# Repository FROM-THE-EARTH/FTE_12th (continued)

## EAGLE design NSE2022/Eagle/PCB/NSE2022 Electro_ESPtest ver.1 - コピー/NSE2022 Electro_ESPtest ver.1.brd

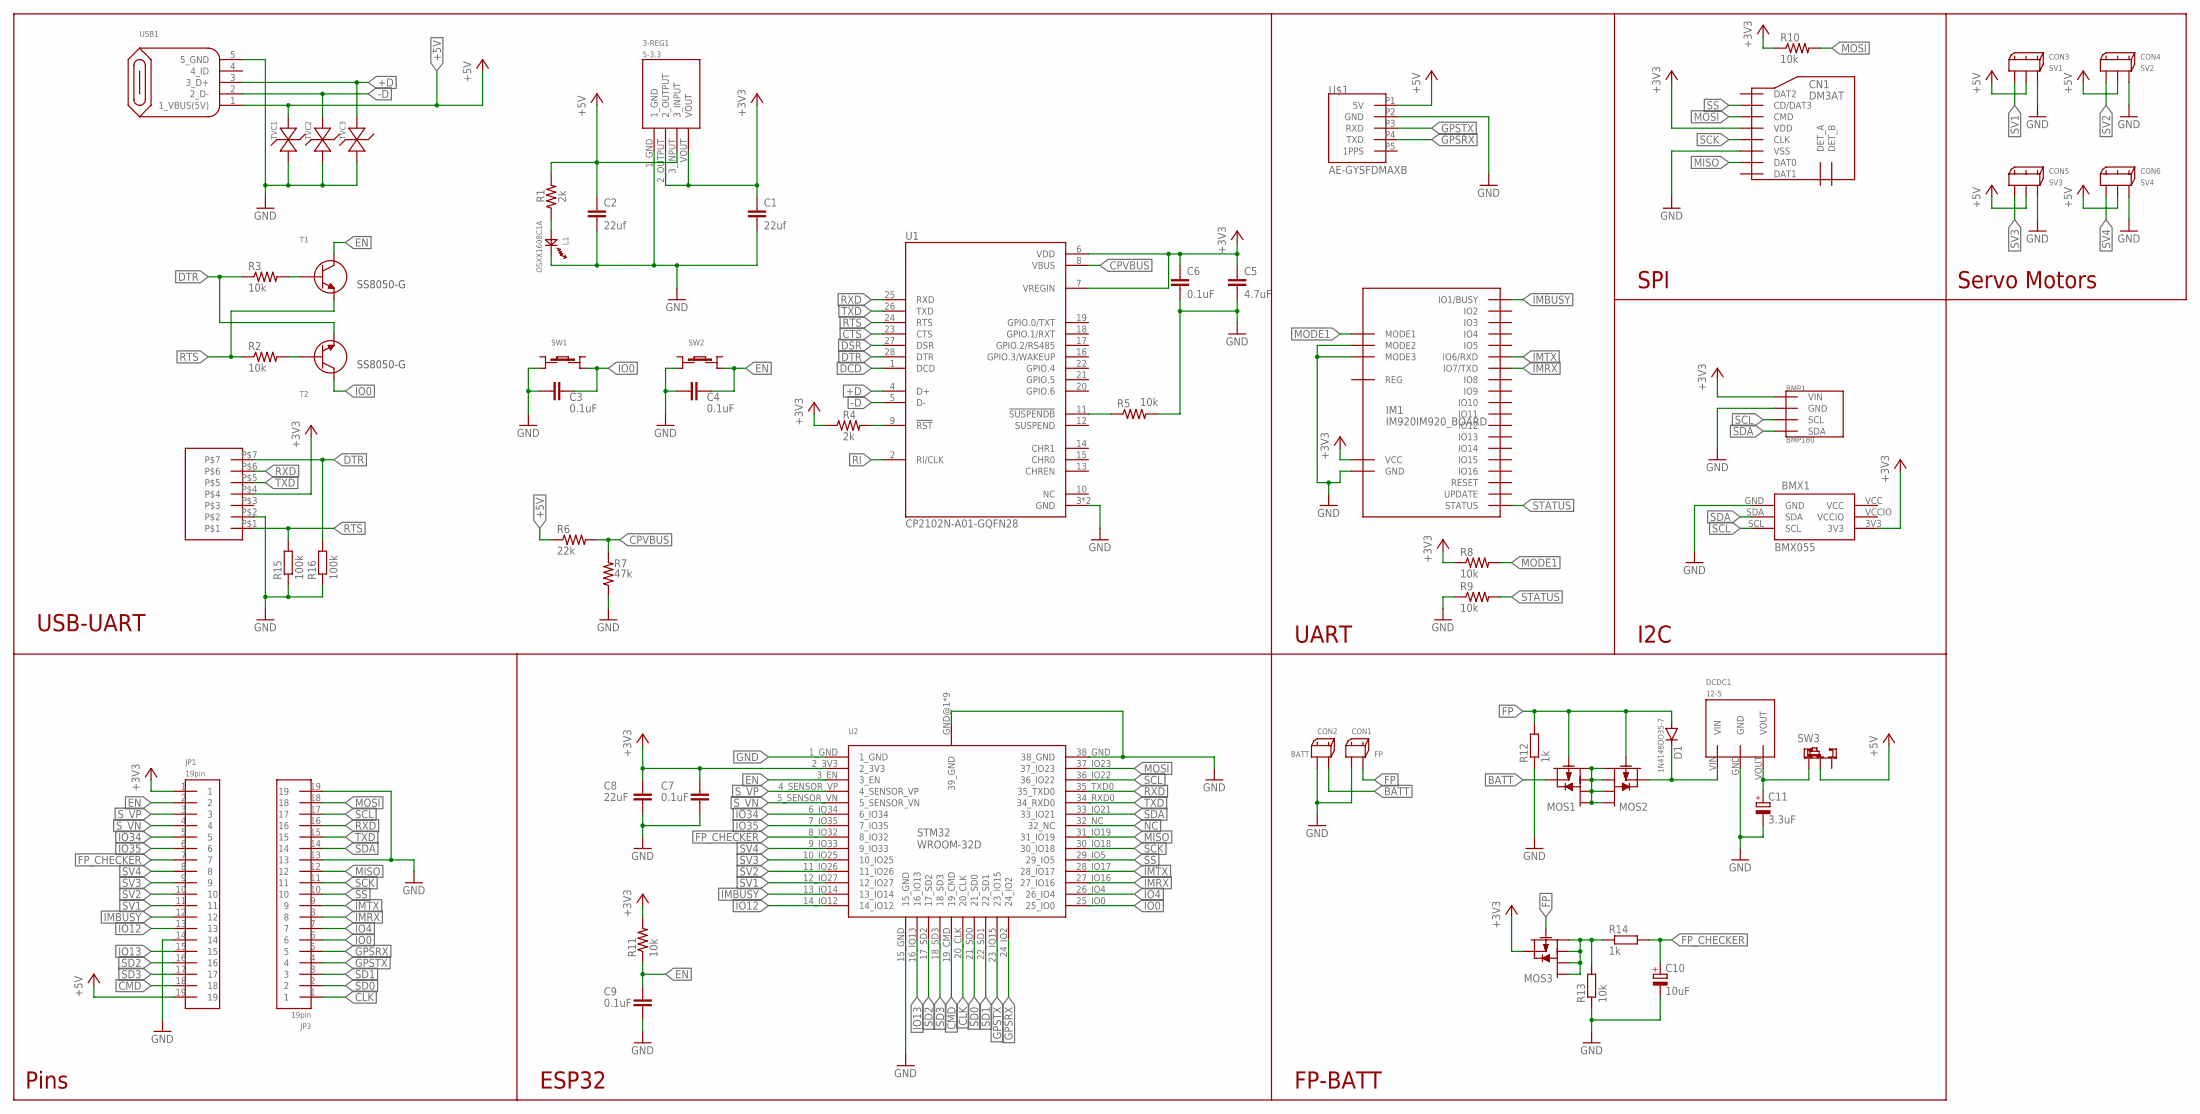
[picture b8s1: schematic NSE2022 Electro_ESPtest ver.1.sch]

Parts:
3-REG1: 5-3.3; AZ1117CH-3.3TRG1
BMP1: BMP180; GY-68
BMX1: BMX055
C1, C2: 22uf; C0603
C3, C4, C6, C7, C9: 0.1uF; C0603
C5: 4.7uF; C0402
C8: 22uF; C0603
C10: 10uF; E2,5-5
C11: 3.3uF; E2,5-5
CN1: DM3AT
CON1: FP; 2.5_MINI-SPOX_2PIN
CON2: BATT; 2.5_MINI-SPOX_2PIN
CON3: SV1; 2.5_MINI-SPOX_3PIN
CON4: SV2; 2.5_MINI-SPOX_3PIN
CON5: SV3; 2.5_MINI-SPOX_3PIN
CON6: SV4; 2.5_MINI-SPOX_3PIN
D1: 1N4148DO35-7; DO35-7
DCDC1: 12-5; 5V1A_M78AR05-1
IM1: IM920IM920_BOARD; IM920_BOARD
JP1, JP3: 19pin; 19_2.54
JP2: 7pin; 7_2.54
L1: OSXX1608C1A
MOS1, MOS2, MOS3: PCH_SSM6J808R; SSM6J808R
R1, R4: 2k; R0201
R2, R3, R5, R8, R9, R10, R11: 10k; R0201
R6: 22k; R0201
R7: 47k; R0201
R12, R14: 1k; 0207/10
R13: 10k; 0207/10
R15, R16: 100k; 0207/10
SW1, SW2: TS-06104
SW3: SRIDE_SWITCH
T1, T2: NPN_SS8050-G
TVC1, TVC2, TVC3: ESD5484FCT5G
U1: CP2102N-A01-GQFN28; QFN50P500X500X80-29N
U2: ESP32-WROOM-32D
U$1: AE-GYSFDMAXB
USB1: MICRO-B_ZX62R-B-5P

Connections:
+3V3: 3-REG1.2_OUTPUT, 3-REG1.VOUT, BMP1.P1 (VIN), BMX1.3V3, C1.1, C5.1, C6.1, C7.1, C8.1, CN1.VDD, IM1.IO23 (VCC), JP1.1, JP2.P$4, MOS3.S, R4.1, R8.1, R10.1, R11.2, U1.6 (VDD), U1.7 (VREGIN), U2.2_3V3
+5V: 3-REG1.3_INPUT, C2.1, CON3.2, CON4.2, CON5.2, CON6.2, JP1.19, R1.2, R6.1, SW3.LR, TVC1.2_AN, U$1.P1 (5V), USB1.1 (1_VBUS(5V))
+D: TVC3.2_AN, U1.4 (D+), USB1.3 (3_D+)
-D: TVC2.2_AN, U1.5 (D-), USB1.2 (2_D-)
BATT: CON2.2, MOS1.S
CLK: JP3.1, U2.20_CLK
CMD: JP1.18, U2.19_CMD
CPVBUS: R6.2, R7.2, U1.8 (VBUS)
CTS: U1.23 (CTS)
DCD: U1.1 (DCD)
DSR: U1.27 (DSR)
DTR: JP2.P$7, R3.1, R16.2, T2.2, U1.28 (DTR)
EN: C4.1, C9.1, JP1.2, R11.1, SW2.D, T1.3, U2.3_EN
FP: CON1.2, D1.A, MOS1.G, MOS2.G, MOS3.G, R12.2
FP_CHECKER: C10.+, JP1.7, R14.2, U2.8_IO32
GND: 3-REG1.1_GND, BMP1.P2 (GND), BMX1.GND, C1.2, C2.2, C3.2, C4.2, C5.2, C6.2, C7.2, C8.2, C9.2, C10.-, C11.-, CN1.VSS, CON1.1, CON2.1, CON3.3, CON4.3, CON5.3, CON6.3, DCDC1.GND, IM1.IO18 (MODE2), IM1.IO19 (MODE3), IM1.IO24 (GND), JP1.14, JP2.P$2, JP3.13, JP3.19, L1.CT, R5.2, R7.1, R9.1, R12.1, R13.1, R15.1, R16.1, SW1.B, SW2.B, TVC1.1_CT, TVC2.1_CT, TVC3.1_CT, U1.3 (GND), U1.29 (GND), U2.1_GND, U2.15_GND, U2.38_GND, U2.GND@1 (39_GND), U2.GND@2 (39_GND), U2.GND@3 (39_GND), U2.GND@4 (39_GND), U2.GND@5 (39_GND), U2.GND@6 (39_GND), U2.GND@7 (39_GND), U2.GND@8 (39_GND), U2.GND@9 (39_GND), U$1.P2 (GND), USB1.5 (5_GND)
GPSRX: JP3.5, U2.24_IO2, U$1.P4 (TXD)
GPSTX: JP3.4, U2.23_IO15, U$1.P3 (RXD)
IMBUSY: IM1.IO1 (IO1/BUSY), JP1.12, U2.13_IO14
IMRX: IM1.IO7 (IO7/TXD), JP3.8, U2.27_IO16
IMTX: IM1.IO6 (IO6/RXD), JP3.9, U2.28_IO17
IO0: C3.1, JP3.6, SW1.D, T2.3, U2.25_IO0
IO4: JP3.7, U2.26_IO4
IO12: JP1.13, U2.14_IO12
IO13: JP1.15, U2.16_IO13
IO34: JP1.5, U2.6_IO34
IO35: JP1.6, U2.7_IO35
MISO: CN1.DAT0, JP3.12, U2.31_IO19
MODE1: IM1.IO17 (MODE1), R8.2
MOSI: CN1.CMD, JP3.18, R10.2, U2.37_IO23
unnamed: L1.AN, R1.1
unnamed: R3.2, T1.1
unnamed: R2.2, T2.1
unnamed: R4.2, U1.9 (!RST)
unnamed: R5.1, U1.11 (!SUSPENDB)
unnamed: D1.C, DCDC1.VIN, MOS2.S
unnamed: MOS1.D1, MOS1.D2, MOS1.D3, MOS1.D4, MOS2.D1, MOS2.D2, MOS2.D3, MOS2.D4
unnamed: C11.+, DCDC1.VOUT, SW3.L
unnamed: MOS3.D1, MOS3.D2, MOS3.D3, MOS3.D4, R13.2, R14.1
NC: U2.32_NC
RI: U1.2 (RI/CLK)
RTS: JP2.P$1, R2.1, R15.2, T1.2, U1.24 (RTS)
RXD: JP2.P$6, JP3.16, U1.25 (RXD), U2.35_TXD0
SCK: CN1.CLK, JP3.11, U2.30_IO18
SCL: BMP1.P3 (SCL), BMX1.SCL, JP3.17, U2.36_IO22
SD0: JP3.2, U2.21_SD0
SD1: JP3.3, U2.22_SD1
SD2: JP1.16, U2.17_SD2
SD3: JP1.17, U2.18_SD3
SDA: BMP1.P4 (SDA), BMX1.SDA, JP3.14, U2.33_IO21
SS: CN1.CD/DAT3, JP3.10, U2.29_IO5
STATUS: IM1.IO21 (STATUS), R9.2
SV1: CON3.1, JP1.11, U2.12_IO27
SV2: CON4.1, JP1.10, U2.11_IO26
SV3: CON5.1, JP1.9, U2.10_IO25
SV4: CON6.1, JP1.8, U2.9_IO33
S_VN: JP1.4, U2.5_SENSOR_VN
S_VP: JP1.3, U2.4_SENSOR_VP
TXD: JP2.P$5, JP3.15, U1.26 (TXD), U2.34_RXD0
VCC: BMX1.VCC
VCCIO: BMX1.VCCIO

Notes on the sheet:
USB-UART
Pins
ESP32
UART
I2C
SPI
SS8050-G
FP-BATT
Servo Motors

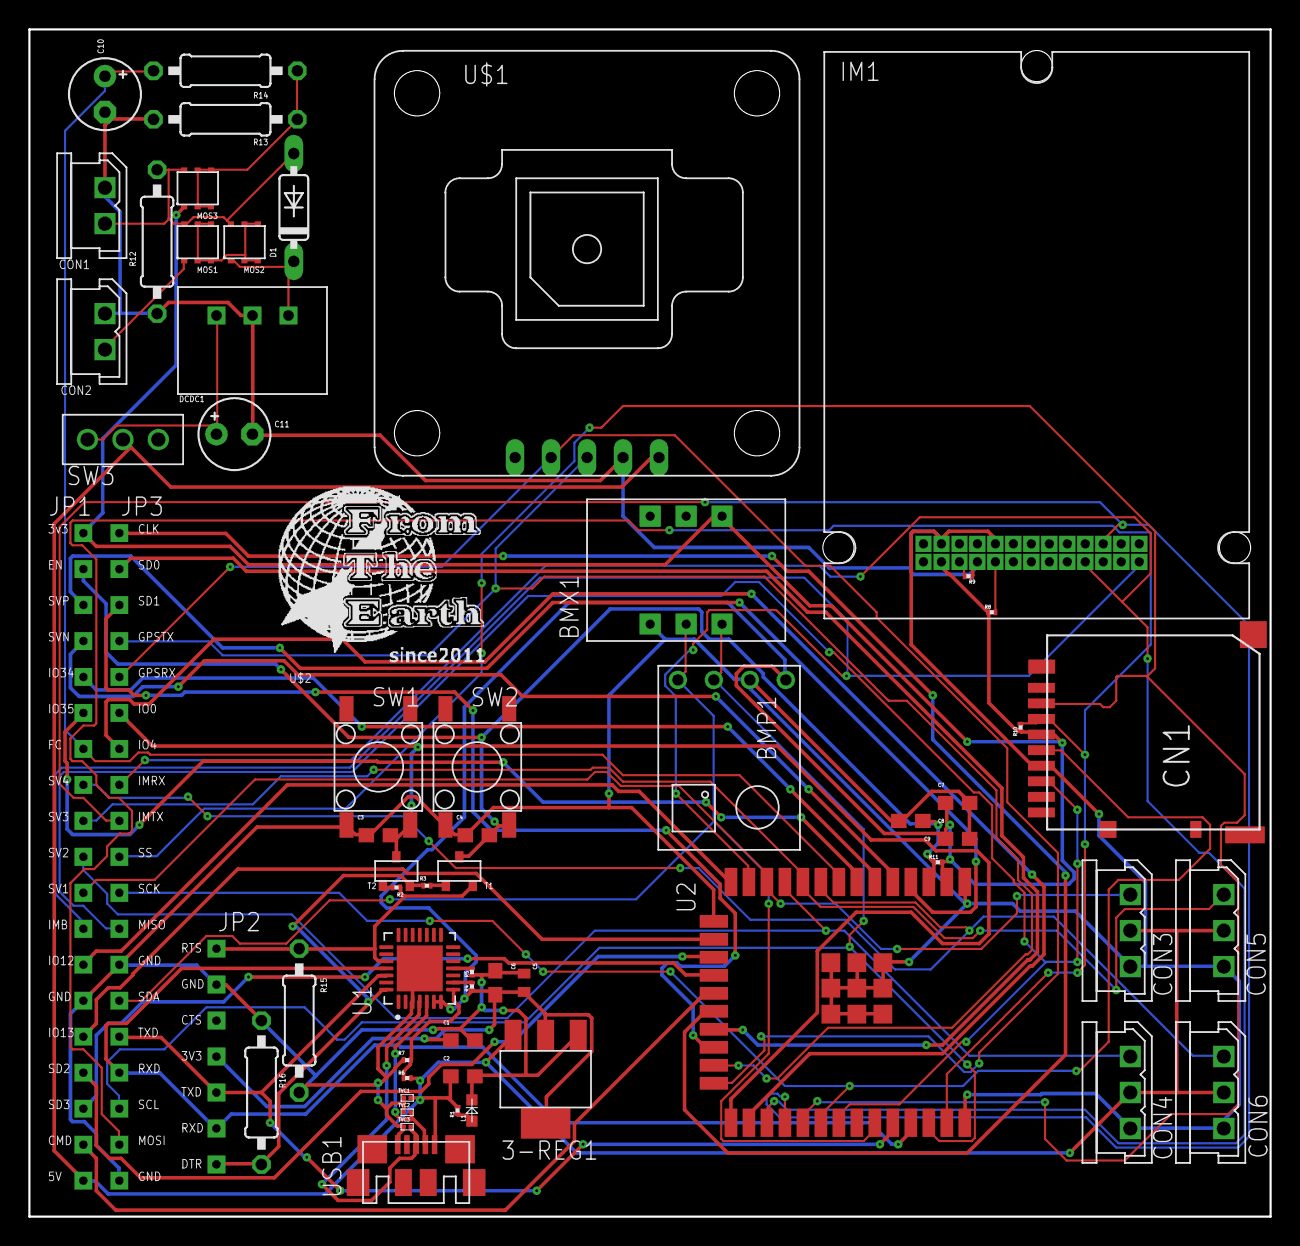
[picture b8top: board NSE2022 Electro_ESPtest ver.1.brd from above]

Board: 2 copper layers, 87.6 x 83.8 mm, 60 parts (0 on the bottom side), 54 nets.

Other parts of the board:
U$2: LOGO
